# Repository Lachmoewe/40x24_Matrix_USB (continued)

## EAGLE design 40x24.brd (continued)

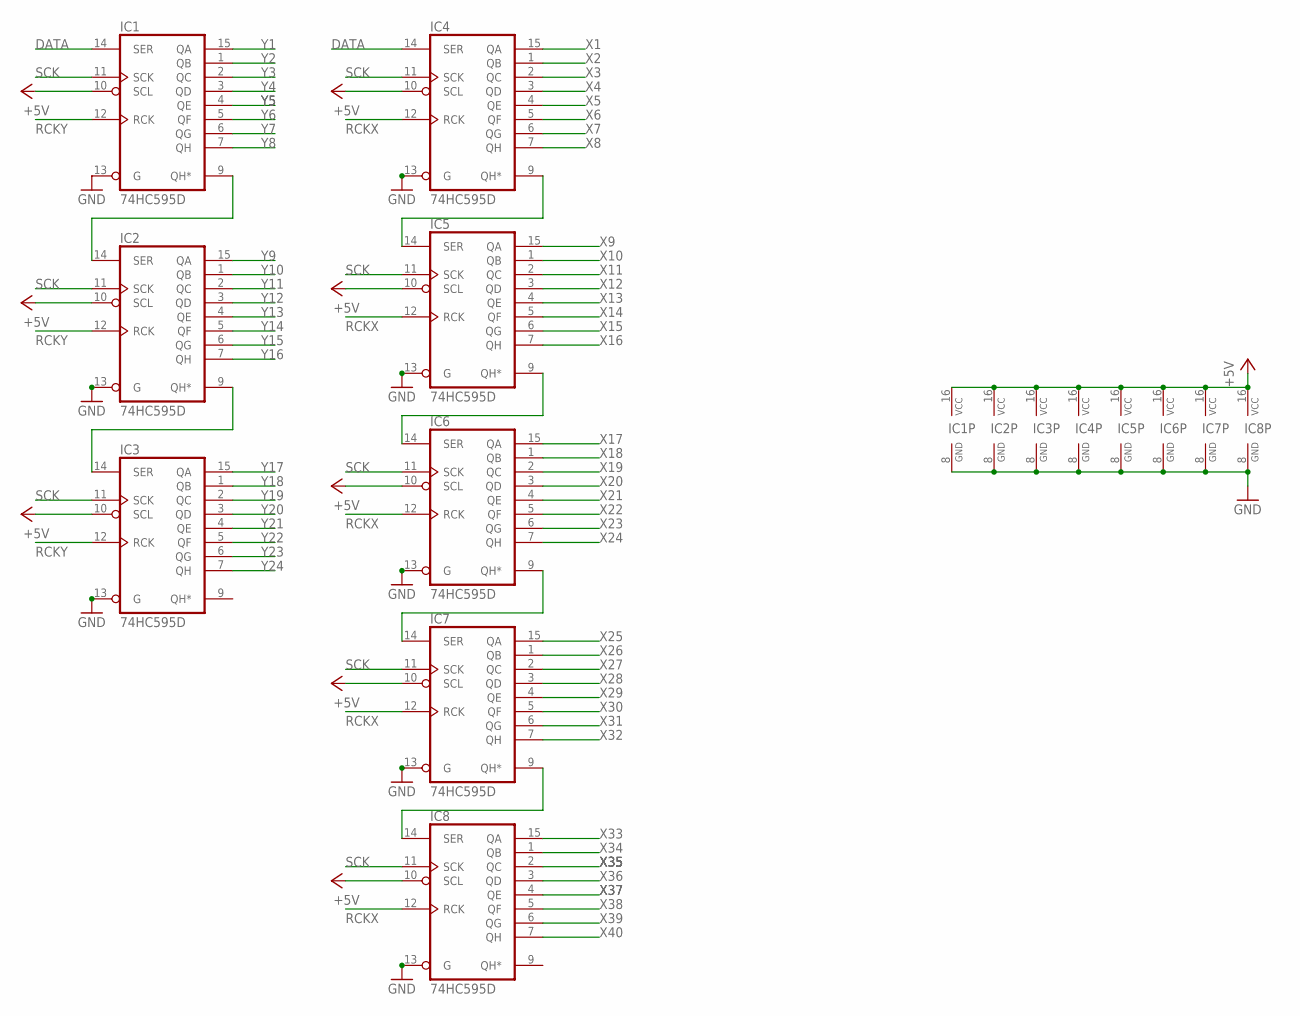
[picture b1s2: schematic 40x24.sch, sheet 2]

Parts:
IC1, IC2, IC3, IC4, IC5, IC6, IC7, IC8: 74HC595D; SO16

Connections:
+5V: IC1.10 (SCL), IC1.16 (VCC), IC2.10 (SCL), IC2.16 (VCC), IC3.10 (SCL), IC3.16 (VCC), IC4.10 (SCL), IC4.16 (VCC), IC5.10 (SCL), IC5.16 (VCC), IC6.10 (SCL), IC6.16 (VCC), IC7.10 (SCL), IC7.16 (VCC), IC8.10 (SCL), IC8.16 (VCC); also elsewhere on the board
DATA: IC1.14 (SER), IC4.14 (SER); also elsewhere on the board
GND: IC1.8 (GND), IC1.13 (G), IC2.8 (GND), IC2.13 (G), IC3.8 (GND), IC3.13 (G), IC4.8 (GND), IC4.13 (G), IC5.8 (GND), IC5.13 (G), IC6.8 (GND), IC6.13 (G), IC7.8 (GND), IC7.13 (G), IC8.8 (GND), IC8.13 (G); also elsewhere on the board
unnamed: IC4.9 (QH*), IC5.14 (SER)
unnamed: IC5.9 (QH*), IC6.14 (SER)
unnamed: IC6.9 (QH*), IC7.14 (SER)
unnamed: IC7.9 (QH*), IC8.14 (SER)
unnamed: IC1.9 (QH*), IC2.14 (SER)
unnamed: IC2.9 (QH*), IC3.14 (SER)
RCKX: IC4.12 (RCK), IC5.12 (RCK), IC6.12 (RCK), IC7.12 (RCK), IC8.12 (RCK); also elsewhere on the board
RCKY: IC1.12 (RCK), IC2.12 (RCK), IC3.12 (RCK); also elsewhere on the board
SCK: IC1.11 (SCK), IC2.11 (SCK), IC3.11 (SCK), IC4.11 (SCK), IC5.11 (SCK), IC6.11 (SCK), IC7.11 (SCK), IC8.11 (SCK); also elsewhere on the board
X1: IC4.15 (QA); also elsewhere on the board
X2: IC4.1 (QB); also elsewhere on the board
X3: IC4.2 (QC); also elsewhere on the board
X4: IC4.3 (QD); also elsewhere on the board
X5: IC4.4 (QE); also elsewhere on the board
X6: IC4.5 (QF); also elsewhere on the board
X7: IC4.6 (QG); also elsewhere on the board
X8: IC4.7 (QH); also elsewhere on the board
X9: IC5.15 (QA); also elsewhere on the board
X10: IC5.1 (QB); also elsewhere on the board
X11: IC5.2 (QC); also elsewhere on the board
X12: IC5.3 (QD); also elsewhere on the board
X13: IC5.4 (QE); also elsewhere on the board
X14: IC5.5 (QF); also elsewhere on the board
X15: IC5.6 (QG); also elsewhere on the board
X16: IC5.7 (QH); also elsewhere on the board
X17: IC6.15 (QA); also elsewhere on the board
X18: IC6.1 (QB); also elsewhere on the board
X19: IC6.2 (QC); also elsewhere on the board
X20: IC6.3 (QD); also elsewhere on the board
X21: IC6.4 (QE); also elsewhere on the board
X22: IC6.5 (QF); also elsewhere on the board
X23: IC6.6 (QG); also elsewhere on the board
X24: IC6.7 (QH); also elsewhere on the board
X25: IC7.15 (QA); also elsewhere on the board
X26: IC7.1 (QB); also elsewhere on the board
X27: IC7.2 (QC); also elsewhere on the board
X28: IC7.3 (QD); also elsewhere on the board
X29: IC7.4 (QE); also elsewhere on the board
X30: IC7.5 (QF); also elsewhere on the board
X31: IC7.6 (QG); also elsewhere on the board
X32: IC7.7 (QH); also elsewhere on the board
X33: IC8.15 (QA); also elsewhere on the board
X34: IC8.1 (QB); also elsewhere on the board
X35: IC8.2 (QC); also elsewhere on the board
X36: IC8.3 (QD); also elsewhere on the board
X37: IC8.4 (QE); also elsewhere on the board
X38: IC8.5 (QF); also elsewhere on the board
X39: IC8.6 (QG); also elsewhere on the board
X40: IC8.7 (QH); also elsewhere on the board
Y1: IC1.15 (QA); also elsewhere on the board
Y2: IC1.1 (QB); also elsewhere on the board
Y3: IC1.2 (QC); also elsewhere on the board
Y4: IC1.3 (QD); also elsewhere on the board
Y5: IC1.4 (QE); also elsewhere on the board
Y6: IC1.5 (QF); also elsewhere on the board
Y7: IC1.6 (QG); also elsewhere on the board
Y8: IC1.7 (QH); also elsewhere on the board
Y9: IC2.15 (QA); also elsewhere on the board
Y10: IC2.1 (QB); also elsewhere on the board
Y11: IC2.2 (QC); also elsewhere on the board
Y12: IC2.3 (QD); also elsewhere on the board
Y13: IC2.4 (QE); also elsewhere on the board
Y14: IC2.5 (QF); also elsewhere on the board
Y15: IC2.6 (QG); also elsewhere on the board
Y16: IC2.7 (QH); also elsewhere on the board
Y17: IC3.15 (QA); also elsewhere on the board
Y18: IC3.1 (QB); also elsewhere on the board
Y19: IC3.2 (QC); also elsewhere on the board
Y20: IC3.3 (QD); also elsewhere on the board
Y21: IC3.4 (QE); also elsewhere on the board
Y22: IC3.5 (QF); also elsewhere on the board
Y23: IC3.6 (QG); also elsewhere on the board
Y24: IC3.7 (QH); also elsewhere on the board

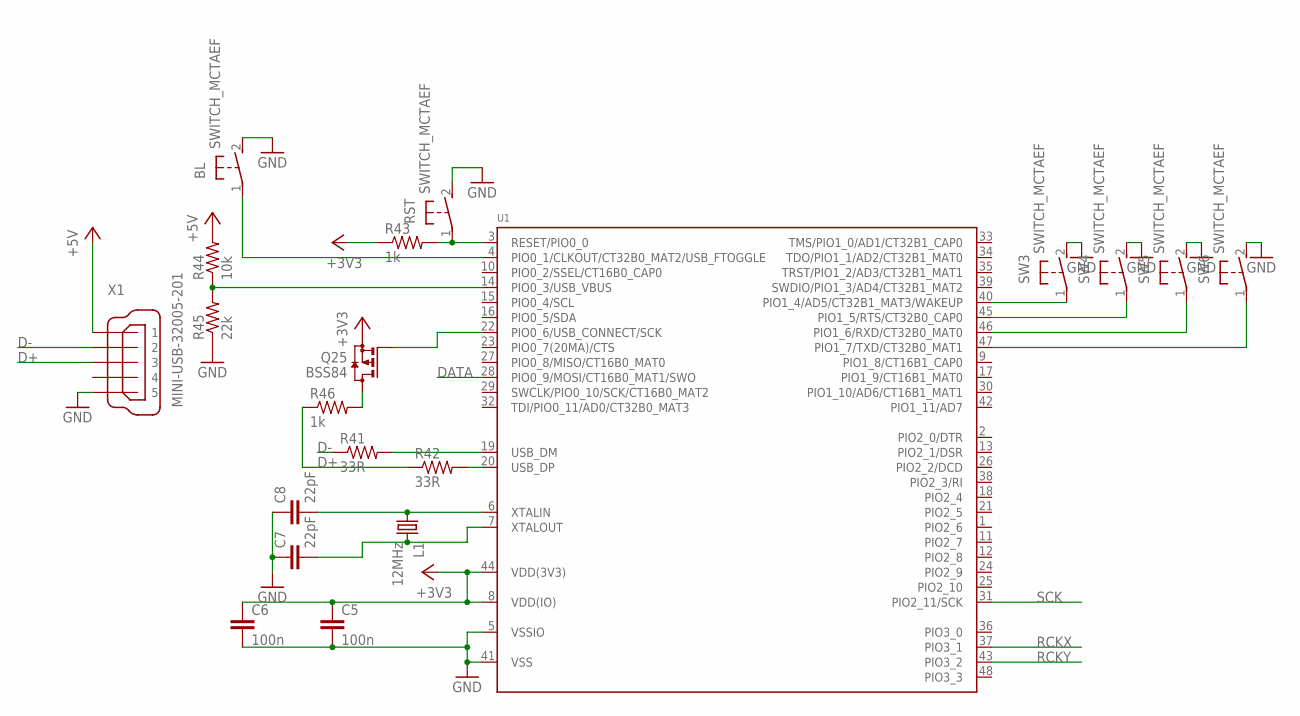
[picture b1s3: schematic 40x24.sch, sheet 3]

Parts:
BL: SWITCH_MCTAEF
C5, C6: 100n; 0805
C7, C8: 22pF; 0805
L1: 12MHz; X22
Q25: BSS84; SOT23
R41, R42: 33R; 0805
R43, R46: 1k; 0805
R44: 10k; 0805
R45: 22k; 0805
RST: SWITCH_MCTAEF
SW3, SW4, SW5, SW6: SWITCH_MCTAEF
U1: LPC1343_QFP; LQFP48
X1: MINI-USB-32005-201; 32005-201

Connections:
+3V3: C5.1, C6.1, Q25.2 (S), R43.1, U1.8 (VDD(IO)), U1.44 (VDD(3V3)); also elsewhere on the board
+5V: R44.2, X1.1; also elsewhere on the board
D+: R42.1, R46.1, X1.3
D-: R41.1, X1.2
DATA: U1.28 (PIO0_9/MOSI/CT16B0_MAT1/SWO); also elsewhere on the board
GND: BL.2, C5.2, C6.2, C7.1, C8.1, R45.1, RST.2, SW3.2, SW4.2, SW5.2, SW6.2, U1.5 (VSSIO), U1.41 (VSS), X1.5; also elsewhere on the board
unnamed: R42.2, U1.20 (USB_DP)
unnamed: R41.2, U1.19 (USB_DM)
unnamed: R43.2, RST.1, U1.3 (RESET/PIO0_0)
unnamed: C7.2, L1.3 (2), U1.7 (XTALOUT)
unnamed: C8.2, L1.1, U1.6 (XTALIN)
unnamed: BL.1, U1.4 (PIO0_1/CLKOUT/CT32B0_MAT2/USB_FTOGGLE)
unnamed: SW3.1, U1.40 (PIO1_4/AD5/CT32B1_MAT3/WAKEUP)
unnamed: SW4.1, U1.45 (PIO1_5/RTS/CT32B0_CAP0)
unnamed: Q25.1 (G), U1.22 (PIO0_6/USB_CONNECT/SCK)
unnamed: R44.1, R45.2, U1.14 (PIO0_3/USB_VBUS)
unnamed: Q25.3 (D), R46.2
unnamed: SW5.1, U1.46 (PIO1_6/RXD/CT32B0_MAT0)
unnamed: SW6.1, U1.47 (PIO1_7/TXD/CT32B0_MAT1)
RCKX: U1.37 (PIO3_1); also elsewhere on the board
RCKY: U1.43 (PIO3_2); also elsewhere on the board
SCK: U1.31 (PIO2_11/SCK); also elsewhere on the board

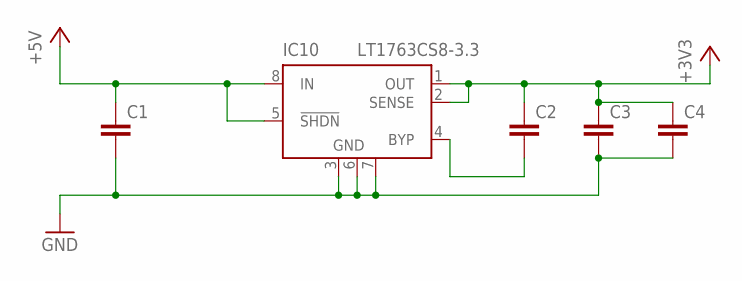
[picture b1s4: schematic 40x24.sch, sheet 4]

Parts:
C1, C2, C3, C4: CAP0805; 0805
IC10: LT1763CS8-3.3; SOIC8

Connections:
+3V3: C2.1, C3.1, C4.1, IC10.1 (OUT), IC10.2 (SENSE); also elsewhere on the board
+5V: C1.1, IC10.5 (!SHDN), IC10.8 (IN); also elsewhere on the board
GND: C1.2, C3.2, C4.2, IC10.3 (GND), IC10.6 (GND), IC10.7 (GND); also elsewhere on the board
unnamed: C2.2, IC10.4 (BYP)

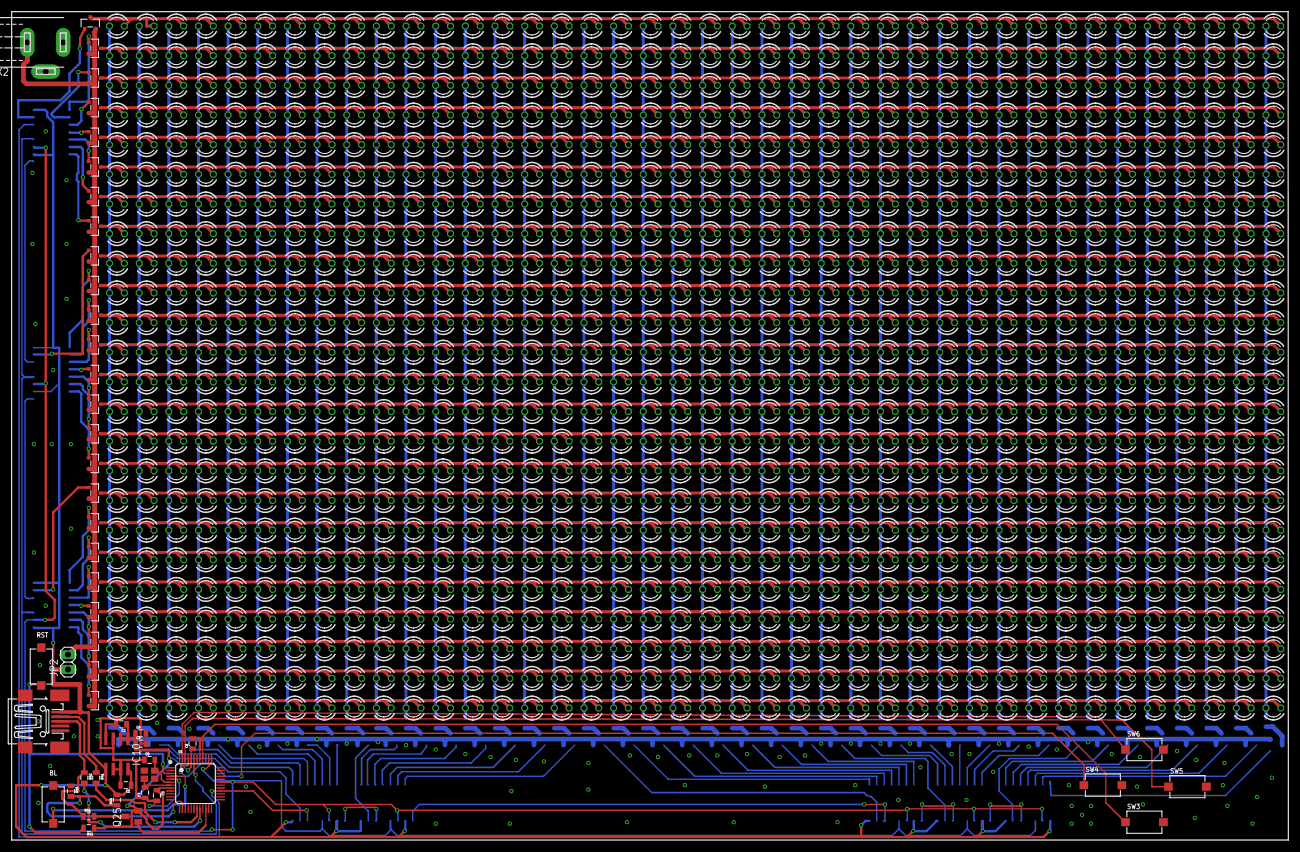
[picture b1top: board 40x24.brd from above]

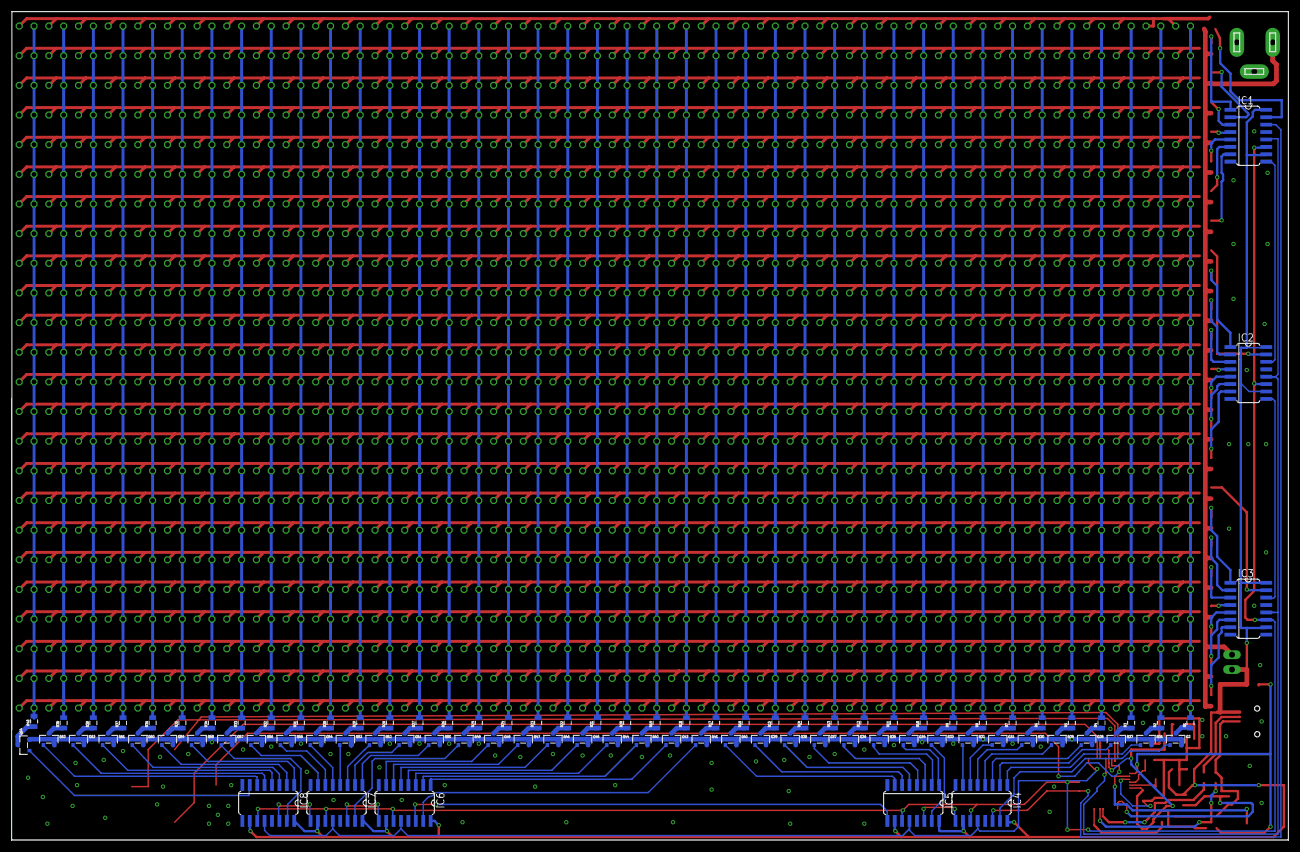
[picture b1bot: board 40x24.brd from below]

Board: 2 copper layers, 218.7 x 141.9 mm, 1099 parts (88 on the bottom side), 198 nets.

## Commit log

2012-09-13 initial
